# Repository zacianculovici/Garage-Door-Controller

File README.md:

# Garage-Door-Controller

## What it is
An ESP32-C3 based bluetooth controller for an old B&amp;D roller door. Also works as a standard devboard. 

## Inspiration
I started this project because I had an old roller door and the remote was playing up. I prototyped it with a normal ESP32 on a breadboard, and decided to make a better version on one PCB with a case. I am both nervous and excited to get it made as I have never made a proper PCB this complicated before. 

## Parts
### Schematics
Garage-Door-Controller is essentially just a ESP32-C3 devboard, with an on-board optocoupler to short the pins of the up/down button on the roller door. Because JLCPCB has a minumum PCB assembly quantity of 2, I plan to use one as the controller, and the other as a normal devboard with an inbuilt optocoupler. 

### PCB
The PCB is designed to be as small as possible, and it is really just a standard ESP32-C3 devboard that I designed, but I added two mounting holes and two sets of pin headers which is a bit custom. 

### [Case](https://cad.onshape.com/documents/283e0c7c058a35166ead487a/w/4066f8a87f001ae32717c400/e/d57d04382974445a9a2175db)
The case is a simple 3D printed case, and I decided to make it translucent because it will look really nice. I made flexible button actuators and a screw wall hanger, and it will be screwed together with M3 bolts and heatset inserts. 

### BOM
Here is the [full BOM](https://github.com/zacianculovici/Garage-Door-Controller/blob/main/BOM.csv)
| Part                      | Type       | Quantity | Unit price aud | Line total aud | Link                                                         | Vendor                      | Funding     | Notes                             | Quantity needed | Value               | Lcsc      |
| :------------------------ | :--------- | :------- | :------------- | :------------- | :----------------------------------------------------------- | :-------------------------- | :---------- | :-------------------------------- | :-------------- | :------------------ | :-------- |
| C2,C5                     | Part       | 20       | 0.029          | 0.58           | https://jlcpcb.com/parts/componentSearch?searchTxt=C15525    | JLCPCB                      | Grant       |                                   | 2               | 10uF                | C15525    |
| SW1,SW3                   | Part       | 14       | 0.0761         | 1.0654         | https://jlcpcb.com/parts/componentSearch?searchTxt=C720477   | JLCPCB                      | Grant       |                                   | 2               | BOOT,RST            | C720477   |
| C19,C21                   | Part       | 20       | 0.0037         | 0.074          | https://jlcpcb.com/parts/componentSearch?searchTxt=C1547     | JLCPCB                      | Grant       |                                   | 2               | 12pF                | C1547     |
| R8                        | Part       | 20       | 0.0016         | 0.032          | https://jlcpcb.com/parts/componentSearch?searchTxt=C25104    | JLCPCB                      | Grant       |                                   | 1               | 330R                | C25104    |
| U7                        | Part       | 5        | 0.0022         | 0.011          | https://jlcpcb.com/parts/componentSearch?searchTxt=C1870448  | JLCPCB                      | Grant       |                                   | 1               | 40MHz               | C1870448  |
| R4,R10                    | Part       | 20       | 0.0043         | 0.086          | https://jlcpcb.com/parts/componentSearch?searchTxt=C25087    | JLCPCB                      | Grant       |                                   | 2               | 200R                | C25087    |
| R3,R7                     | Part       | 25       | 0.0021         | 0.0525         | https://jlcpcb.com/parts/componentSearch?searchTxt=C25905    | JLCPCB                      | Grant       |                                   | 2               | 5k1                 | C25905    |
| R11,R15,R16,R17           | Part       | 35       | 0.0022         | 0.077          | https://jlcpcb.com/parts/componentSearch?searchTxt=C25744    | JLCPCB                      | Grant       |                                   | 4               | 10k                 | C25744    |
| U2                        | Part       | 9        | 0.1159         | 1.0431         | https://jlcpcb.com/parts/componentSearch?searchTxt=C109227   | JLCPCB                      | Grant       |                                   | 1               | OPTO                | C109227   |
| R5,R6                     | Part       | 25       | 0.0015         | 0.0375         | https://jlcpcb.com/parts/componentSearch?searchTxt=C25092    | JLCPCB                      | Grant       |                                   | 2               | 22R                 | C25092    |
| R9                        | Part       | 20       | 0.0018         | 0.036          | https://jlcpcb.com/parts/componentSearch?searchTxt=C17168    | JLCPCB                      | Grant       |                                   | 1               | 0R                  | C17168    |
| LED1                      | Part       | 20       | 0.0106         | 0.212          | https://jlcpcb.com/parts/componentSearch?searchTxt=C2288     | JLCPCB                      | Grant       |                                   | 1               | BUILTIN             | C2288     |
| LED2                      | Part       | 20       | 0.0114         | 0.228          | https://jlcpcb.com/parts/componentSearch?searchTxt=C2286     | JLCPCB                      | Grant       |                                   | 1               | PWR                 | C2286     |
| U4                        | Part       | 5        | 3.2308         | 16.154         | https://jlcpcb.com/parts/componentSearch?searchTxt=C2858491  | JLCPCB                      | Grant       |                                   | 1               | ESP32-C3FH4         | C2858491  |
| C1,C3,C12,C13,C16,C17,C18 | Part       | 47       | 0.0127         | 0.5969         | https://jlcpcb.com/parts/componentSearch?searchTxt=C307331   | JLCPCB                      | Grant       |                                   | 7               | 0.1uF               | C307331   |
| U1                        | Part       | 5        | 0.2968         | 1.484          | https://jlcpcb.com/parts/componentSearch?searchTxt=C6186     | JLCPCB                      | Grant       |                                   | 1               | AMS1117-3.3         | C6186     |
| USB2                      | Part       | 5        | 0.1019         | 0.5095         | https://jlcpcb.com/parts/componentSearch?searchTxt=C53436595 | JLCPCB                      | Grant       |                                   | 1               | HYCW523-USBC16-735B | C53436595 |
| PCB                       | PCB        | 5        | 2.96           | 2.96           | https://jlcpcb.com                                           | JLCPCB                      | Grant       |                                   | 1               |                     |           |
| Assembly                  | Tax or fee | 2        | 19.6231        | 19.6231        | https://jlcpcb.com                                           | JLCPCB                      | Grant       |                                   | 1               |                     |           |
| Assembly Coupon           | Tax or fee | 1        | -15.75         | -15.75         | https://jlcpcb.com                                           | JLCPCB                      | Grant       | This is the U$10 coupon at JLCPCB | 1               |                     |           |
| Box                       | 3D printed | 1        | 1.44           | 1.44           | https://jlc3dp.com                                           | JLC3DP                      | Grant       |                                   | 1               |                     |           |
| Lid                       | 3D printed | 1        | 0.73           | 0.73           | https://jlc3dp.com                                           | JLC3DP                      | Grant       |                                   | 1               |                     |           |
| Shipping                  | Shipping   | 2        | 2.22           | 4.44           | https://jlcpcb.com                                           | Global Standard Direct Line | Grant       |                                   | 2               |                     |           |
| Heatset Insert            | Part       | 2        | 0              | 0              |                                                              | Me                          | Already own |                                   | 2               | M3x5x4              |           |
| Bolt                      | Part       | 2        | 0              | 0              |                                                              | Me                          | Already own |                                   | 2               | M3x8                |           |
| Total                     |            |          |                | 35.51          |                                                              |                             |             |                                   |                 |                     |           |

## Credits
### AI Usage
While I did use a small amount of AI, this project has <sub></sub> of my own work put into it and I am really proud of it. I used Google Gemini to explain how to make most of the schematic, as I have never done anything like this before, and I needed help understanding the official guidelines as they are confusing to a beginner. It also helped me with some layout tips, like how to place things so they are easy to route. Other than that, I did everything else: schematic, layout and routing, etc. 

---
<sup><sub>2026 - Zac Ianculovici | [Contact](mailto:zachary.ianculovici@gmail.com) | [Slack](https://hackclub.enterprise.slack.com/team/U0BMLT1CFB3)</sub></sup>

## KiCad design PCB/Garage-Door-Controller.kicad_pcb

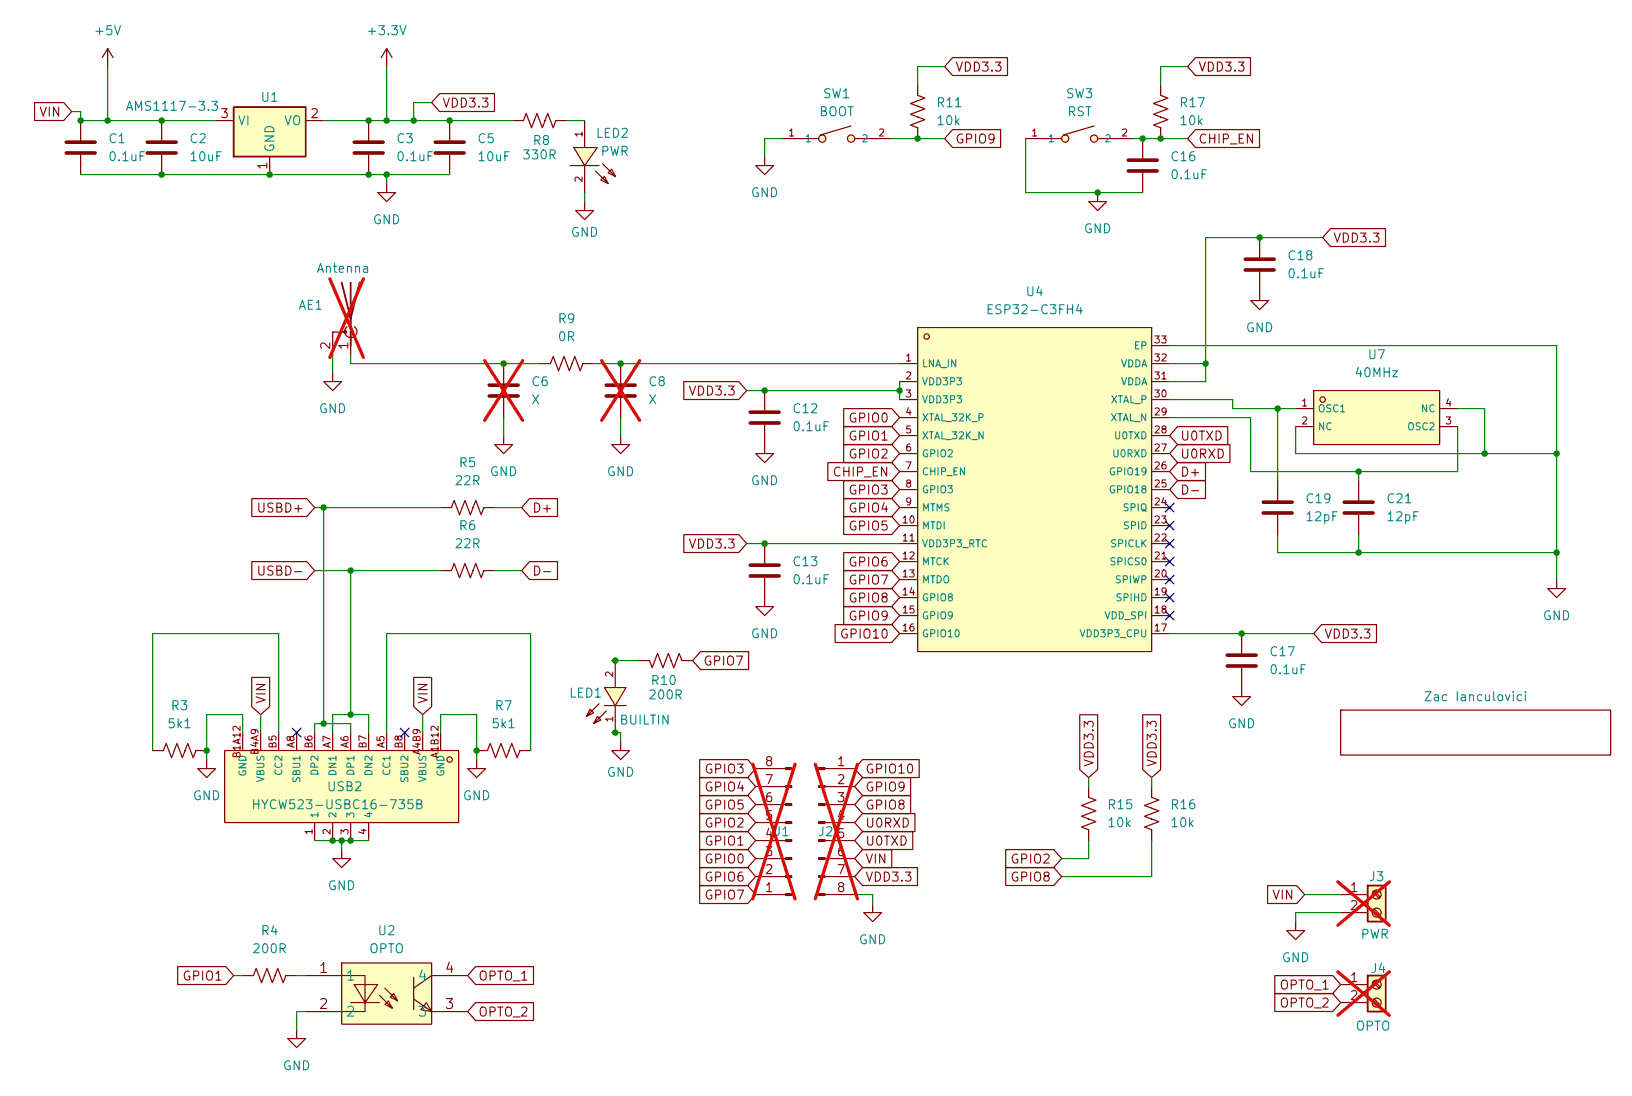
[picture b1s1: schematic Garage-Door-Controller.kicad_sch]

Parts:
1: Zac Ianculovici; LOGO
AE1: Antenna; Texas_SWRA117D_2.4GHz_Left; not fitted
C1, C3, C12, C13, C16, C17, C18: 0.1uF; C_0402_1005Metric; LCSC C307331
C2, C5: 10uF; C_0402_1005Metric; LCSC C15525
C6, C8: X; C_0402_1005Metric; not fitted
C19, C21: 12pF; C_0402_1005Metric; LCSC C1547
J1, J2: Conn_01x08_Pin; PinHeader_1x08_P2.54mm_Vertical; not fitted
J3: PWR; PinHeader_1x02_P2.54mm_Vertical; not fitted
J4: OPTO; PinHeader_1x02_P2.54mm_Vertical; not fitted
LED1: BUILTIN; C72041_LED0603-FD_BLUE; LCSC C72041
LED2: PWR; C2286_LED-SMD_L1_6-W0_8-R-RD; LCSC C2286
R3, R7: 5k1; R_0402_1005Metric; LCSC C25905
R4, R10: 200R; R_0402_1005Metric; LCSC C25087
R5, R6: 22R; R_0402_1005Metric; LCSC C25092
R8: 330R; R_0402_1005Metric; LCSC C25104
R9: 0R; R_0402_1005Metric; LCSC C17168
R11, R15, R16, R17: 10k; R_0402_1005Metric; LCSC C25744
SW1: BOOT; C720477_SW-SMD_L3_9-W3_0-P4_45; LCSC C720477
SW3: RST; C720477_SW-SMD_L3_9-W3_0-P4_45; LCSC C720477
U1: AMS1117-3.3; SOT-223-3_TabPin2; LCSC C6186
U2: OPTO; C109227_OPTO-SMD-4_L4_6-W6_5-P2_54-LS10_3-BL; LCSC C109227
U4: ESP32-C3FH4; C2858491_QFN-32_L5_0-W5_0-P0_50-TL-EP3_7; LCSC C2858491
U7: 40MHz; C1870448_OSC-SMD_4P-L2_0-W1_6-BL_ABRACON_ASTMHTA; LCSC C1870448
USB2: HYCW523-USBC16-735B; C53436595_USB-TYPE-C-SMD_JS16T-TYPE-C057-H730; LCSC C53436595

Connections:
CHIP_EN: C16.1, R17.1, SW3.2, U4.7 (CHIP_EN)
D+: R5.2, U4.26 (GPIO19)
D-: R6.2, U4.25 (GPIO18)
GND: AE1.2 (Shield), C1.2, C2.2, C3.2, C5.2, C6.1, C8.1, C12.2, C13.2, C16.2, C17.2, C18.2, C19.2, C21.2, J2.8, J3.2, LED1.1 (C), LED2.2 (K), R3.2, R7.1, SW1.1, SW3.1, U1.1 (GND), U2.2, U4.33 (EP), U7.2 (NC), U7.4 (NC), USB2.1, USB2.2, USB2.3, USB2.4, USB2.A1B12 (GND), USB2.B1A12 (GND)
GPIO0: J1.3, U4.4 (XTAL_32K_P)
GPIO1: J1.4, R4.1, U4.5 (XTAL_32K_N)
GPIO2: J1.5, R15.2, U4.6 (GPIO2)
GPIO3: J1.8, U4.8 (GPIO3)
GPIO4: J1.7, U4.9 (MTMS)
GPIO5: J1.6, U4.10 (MTDI)
GPIO6: J1.2, U4.12 (MTCK)
GPIO7: J1.1, R10.1, U4.13 (MTDO)
GPIO8: J2.3, R16.2, U4.14 (GPIO8)
GPIO9: J2.2, R11.1, SW1.2, U4.15 (GPIO9)
GPIO10: J2.1, U4.16 (GPIO10)
unnamed: AE1.1 (A), C6.2, R9.1
unnamed: LED1.2 (A), R10.2
unnamed: LED2.1 (A), R8.2
unnamed: R4.2, U2.1
unnamed: C8.2, R9.2, U4.1 (LNA_IN)
unnamed: C21.1, U4.29 (XTAL_N), U7.3 (OSC2)
unnamed: C19.1, U4.30 (XTAL_P), U7.1 (OSC1)
unnamed: R7.2, USB2.A5 (CC1)
unnamed: R3.1, USB2.B5 (CC2)
OPTO_1: J4.1, U2.4
OPTO_2: J4.2, U2.3
U0RXD: J2.4, U4.27 (U0RXD)
U0TXD: J2.5, U4.28 (U0TXD)
USBD+: R5.1, USB2.A6 (DP1), USB2.B6 (DP2)
USBD-: R6.1, USB2.A7 (DN1), USB2.B7 (DN2)
VDD3.3: C3.1, C5.1, C12.1, C13.1, C17.1, C18.1, J2.7, R8.1, R11.2, R15.1, R16.1, R17.2, U1.2 (VO), U4.2 (VDD3P3), U4.3 (VDD3P3), U4.11 (VDD3P3_RTC), U4.17 (VDD3P3_CPU), U4.31 (VDDA), U4.32 (VDDA)
VIN: C1.1, C2.1, J2.6, J3.1, U1.3 (VI), USB2.A4B9 (VBUS), USB2.B4A9 (VBUS)

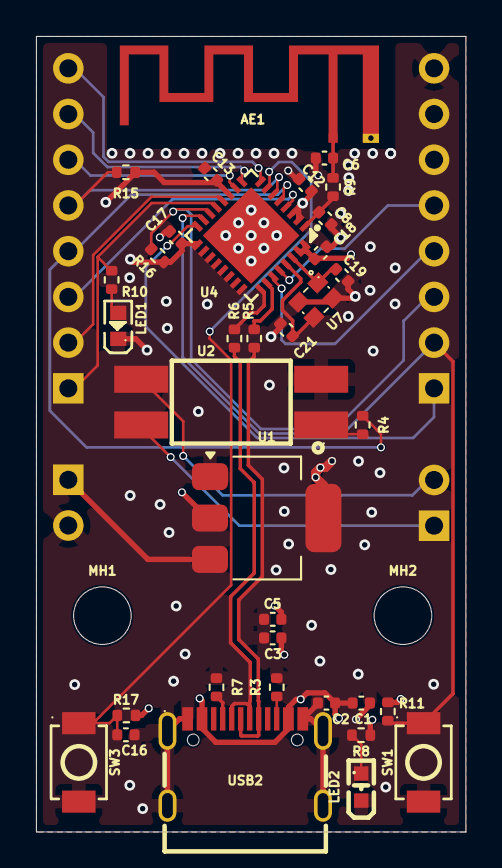
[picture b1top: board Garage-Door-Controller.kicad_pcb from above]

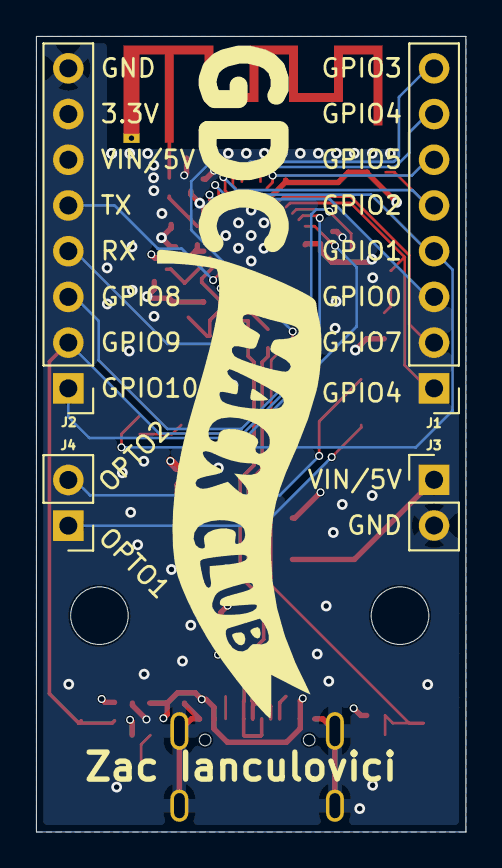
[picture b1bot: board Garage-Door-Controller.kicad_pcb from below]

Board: 4 copper layers, 23.9 x 44.2 mm, 42 parts (5 on the bottom side), 32 nets.

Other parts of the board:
MH1, MH2: MountingHole_3.2mm_M3

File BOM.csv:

Part,Type,Quantity,Unit price (AUD),Line total (AUD),Link,Vendor,Funding,Notes,Quantity Needed,Value,LCSC
"C2,C5",Part,20,0.029,0.58,https://jlcpcb.com/parts,JLCPCB,Grant,,2,10uF,C15525
"SW1,SW3",Part,14,0.0761,1.0654,https://jlcpcb.com/parts,JLCPCB,Grant,,2,"BOOT,RST",C720477
"C19,C21",Part,20,0.0037,0.074,https://jlcpcb.com/parts,JLCPCB,Grant,,2,12pF,C1547
R8,Part,20,0.0016,0.032,https://jlcpcb.com/parts,JLCPCB,Grant,,1,330R,C25104
U7,Part,5,0.0022,0.011,https://jlcpcb.com/parts,JLCPCB,Grant,,1,40MHz,C1870448
R4,Part,20,0.0043,0.086,https://jlcpcb.com/parts,JLCPCB,Grant,,1,200R,C25087
"R3,R7",Part,25,0.0021,0.0525,https://jlcpcb.com/parts,JLCPCB,Grant,,2,5k1,C25905
"R11,R15,R16,R17",Part,35,0.0022,0.077,https://jlcpcb.com/parts,JLCPCB,Grant,,4,10k,C25744
U2,Part,9,0.1159,1.0431,https://jlcpcb.com/parts,JLCPCB,Grant,,1,OPTO,C109227
"R5,R6",Part,25,0.0015,0.0375,https://jlcpcb.com/parts,JLCPCB,Grant,,2,22R,C25092
R9,Part,20,0.0018,0.036,https://jlcpcb.com/parts,JLCPCB,Grant,,1,0R,C17168
LED2,Part,20,0.0114,0.228,https://jlcpcb.com/parts,JLCPCB,Grant,,1,PWR,C2286
U4,Part,5,3.2308,16.154,https://jlcpcb.com/parts,JLCPCB,Grant,,1,ESP32-C3FH4,C2858491
"C1,C3,C12,C13,C16,C17,C18",Part,47,0.0127,0.5969,https://jlcpcb.com/parts,JLCPCB,Grant,,7,0.1uF,C307331
U1,Part,5,0.2968,1.484,https://jlcpcb.com/parts,JLCPCB,Grant,,1,AMS1117-3.3,C6186
USB2,Part,5,0.1019,0.5095,https://jlcpcb.com/parts,JLCPCB,Grant,,1,HYCW523-USBC16-735B,C53436595
PCB,PCB,5,2.96,2.96,https://jlcpcb.com/parts,JLCPCB,Grant,,1,,
Assembly,Tax or fee,2,19.6231,19.6231,https://jlcpcb.com,JLCPCB,Grant,,1,,
Assembly Coupon,Tax or fee,1,-15.75,-15.75,https://jlcpcb.com,JLCPCB,Grant,This is the U$10 coupon at JLCPCB,1,,
Box,3D printed,1,1.44,1.44,https://jlcpcb.com,JLC3DP,Grant,,1,,
Lid,3D printed,1,0.73,0.73,https://jlcpcb.com,JLC3DP,Grant,,1,,
Shipping,Shipping,2,2.22,4.44,https://jlcpcb.com,Global Standard Direct Line,Grant,,2,,
Heatset Insert,Part,2,0.00,0.00,,,Already own,,2,M3x5x4,
Bolt,Part,2,0.00,0.00,,,Already own,,2,M3x8,
Total,,,,35.51,,,,,,,
